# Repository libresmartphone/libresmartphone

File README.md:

Libre Smartphone - Open hardware phone
======================================

This page contains the software used in the open hardware smartphone, related projects files and documentation. Mechanical ([Freecad](http://freecadweb.org/)) and PCB schematic ([Kicad](http://kicad-pcb.org/)) designs will be added here in the future. Visit [libresmartphone.com](http://libresmartphone.com/open-hardware-smartphone/) or our [YouTube channel](https://www.youtube.com/channel/UC1UttFNKDiN2uA525Pe3ijA) for more information.

## Objective

Libresmartphone is a smartphone that can be connected to a bigger screen and used as a desktop computer to edit documents, watch videos, listen to music, edit images, videos and much more.

Our goal is to have a 6" screen, HDMI output, cameras, Bluetooth, WiFi, GPS, 4G or better and GSM. It will also have two or more micro-usb ports that will allow you to connect a printer or other peripherals.

It will be [Open Software](https://en.wikipedia.org/wiki/Open-source_software) and [Open Hardware](https://en.wikipedia.org/wiki/Open-source_hardware), designed with free software (Kicad) to let other users study, change and improve both the software and the hardware.

The design will allow one to add hardware kill switches for the camera, GPS, 4G, GSM.  This offers security & privacy for those who want full control over their devices.

## Roadmap

1. Make a [Raspberry Pi](https://www.raspberrypi.org/) prototype work as desired (Estimated time: 3 months – 1 year)(Estimated cost: <500€):
   * Software to make calls, send/receive SMS (with the [Adafruit 3G Fona](https://www.adafruit.com/product/2696) or similar), import contacts (csv) and take photos in any GNU/linux or BSD OS.
   * GPS navigation with navit.
   * Easy to make case (MDF) / CAD files to 3d print the case.
   * 7" capacitive screen from the Raspberry Pi foundation.
   * Make a manual so every user with a Raspberry Pi can achieve a working prototype easily.

   *The Raspberry Pi prototype will attract a larger user base for the project (currently there are 8 million Raspberry Pi in the market and a lot of their users are DIY enthusiast). Many of them are not willing to pay for an open source smartphone but would love to make calls with the Raspberry Pi, send SMS for their projects, build an simple GPS unit for their car, etc.*

2. Make a prototype with the components more open (Estimated time: 6 months – 4 years)(Estimated cost: 500-40.000€):
   * Use a more open HW board (A64 OLinuXino or similar) instead of the Raspberry Pi.
   * Use a more open HW screen (Manga Screen or similar) or design a 6" capacitive screen if there isn't any open hardware option available at that time (initiate a crowdfunding campaign to let others interested contribute).
   * Use a more open HW modem breakout if there is one available instead of the Adafruit 3G or design a LTE (PLS8-E) or better modem breakout (try to make a crowdfunding campaign to let others interested contribute).

   *The prototype will have replaceable parts if better / smaller alternatives appear in the market.*

   *If no suitable screens or modem breakout are found, a crowdfunding campaign will be made. The reason to make it that way is because there are other people that could want these parts for a different project and help to make it possible faster. Even if there is not enough people willing to support a crowdfunding campaign, the current people interested in making libresmartphone are able to pay Elias Bakken, Nikolaus Schaller or others to make them.*

*When the prototype has the size and requirements desired, libresmartphone development will start part 3.*

3. Libresmartphone final design (Estimated time: <2 years)(Estimated cost: 50.000-200.000€).
   * Design a pcb that has the CPU, GPU, RAM, modem, WiFi, etc in the same board taking in consideration all the designs used in part 2 of the development.
   * Design a case to fit all the components inside that is easy to 3D print. If there are enough people interested an injection case could be made.

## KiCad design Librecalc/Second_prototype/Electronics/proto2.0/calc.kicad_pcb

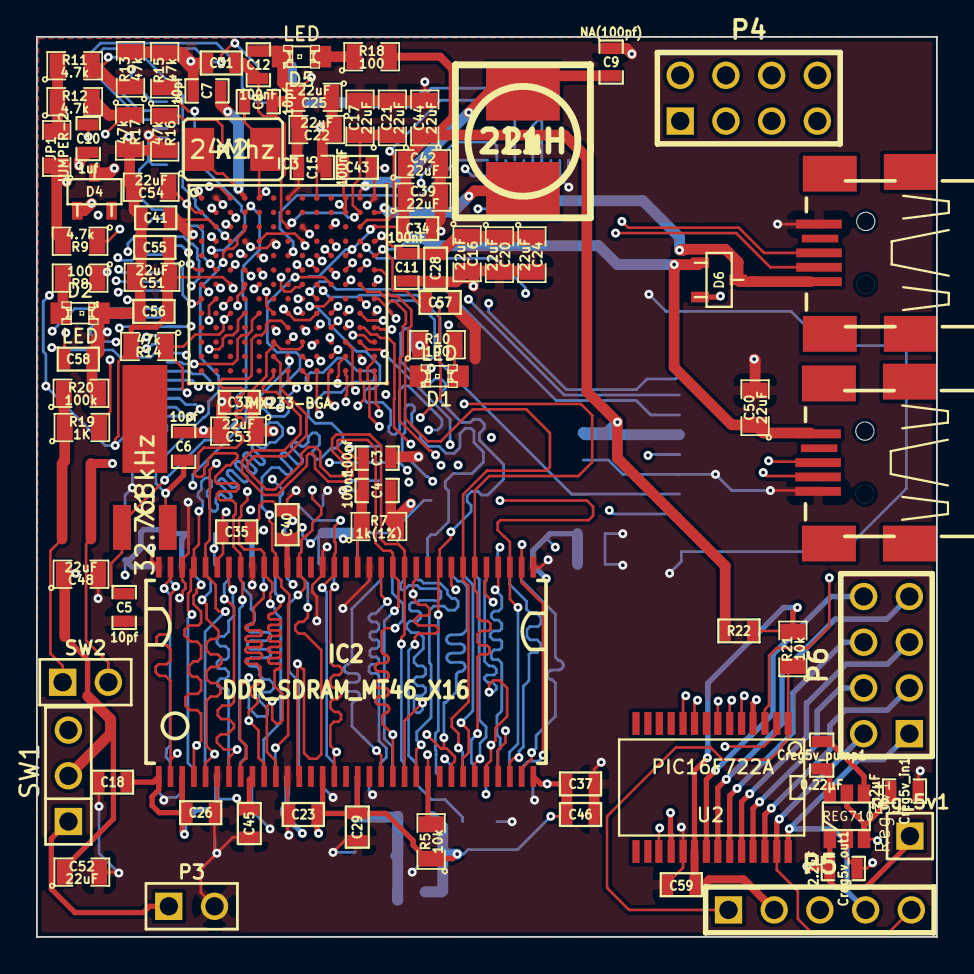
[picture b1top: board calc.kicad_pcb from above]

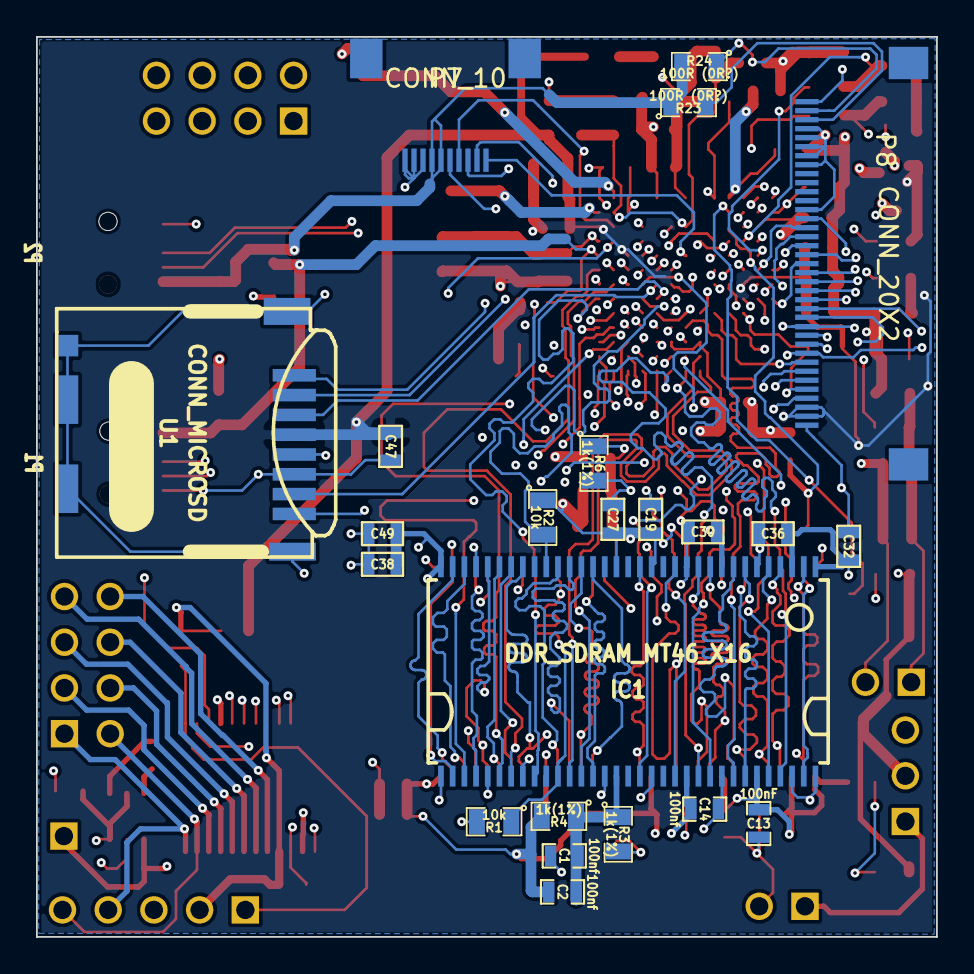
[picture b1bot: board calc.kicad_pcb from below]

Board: 6 copper layers, 50.0 x 50.0 mm, 112 parts (23 on the bottom side), 129 nets.

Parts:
C1, C2, C3, C4, C14: 100nf; SM0603_Capa
C5, C6, C7, C8: 10pf; SM0603_Capa
C9: NA(100pf); SM0603_Capa
C10: 1uf; SM0603_Capa
C11, C12, C13, C15: 100nF; SM0603_Capa
C16, C17, C20, C21, C22, C24, C25, C39, C42, C44, C48, C50, C51, C52, C53, C54: 22uF; SM0805
C18, C23, C27, C30, C32, C36, C38, C41, C59: 100nf; SM0603
C19, C26, C28, C29, C31, C34, C37, C40, C43, C45, C46, C49, C55, C58: 100nF; SM0603
C33, C35, C47, C56, C57: 1uF; SM0603
Creg5v_in1, Creg5v_out1: 2.2µF; SM0603_Capa
Creg5v_pump1: 0.22µF; SM0603_Capa
D1, D2, D5: LED; LED-0805
D4: DIODE; sot23
D6: DOUBLE_SCH_KCOM; sot23
IC1, IC2: DDR_SDRAM_MT46_X16; TSOP66_JEDEC_DDR_SDRAM
IC3: IMX233-BGA; BGA169_0.8mmPitch_11x11mm
JP1: JUMPER-2; SM0805
L1: 22uH; inductor22
P1, P2: CONN_4; CONN_USB_MINI_PIERRE
P3: CONN_2; PIN_ARRAY_2X1
P4, P6: CONN_8; pin_array_4x2
P5: CONN_5; PIN_ARRAY_5x1
P7: CONN_10; FPC10
P8: CONN_20X2; FPC37
R1, R2, R5, R21: 10k; SM0805
R3, R4, R6, R7: 1k(1%); SM0805
R8, R10, R18: 100; SM0805
R9, R11, R12: 4.7k; SM0805
R13, R14, R15, R16, R17: 47k; SM0805
R19: 1K; SM0805
R20: 100k; SM0805
R22: 0R; SM0603
R23, R24: 100R (0R?); SM0805
Reg5v1: REG710; SOT23_6
SW1: SWITCH_INV; PIN_ARRAY_3X1
SW2: SWITCH_PUSHBUTTON; PIN_ARRAY_2X1
U1: CONN_MICROSD; Memory_Card_microSD_DM3CS-SF
U2: PIC16F722A; SSOP28
X1: 32.768kHz; xtal32.768
X2: 24Mhz; SMDXTAL24mhz
reg_5v1: CONN_1; PIN_ARRAY_1

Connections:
3V3PIC: C59.2, P5.2, R21.2, R22.2, U2.20
5VOUT: D6.2, P2.1, P7.6, P7.7, R23.1, R24.2
5VREG: Creg5v_out1.1, D6.3, Reg5v1.1, reg_5v1.1
+2.5V: C2.2, C4.2, C13.1, C14.1, C18.1, C19.1, C23.1, C26.1, C27.1, C29.1, C30.1, C32.1, C33.1, C35.1, C36.1, C37.1, C38.1, C40.1, C45.1, C46.1, C49.1, C53.1, IC1.1, IC1.3, IC1.9, IC1.15, IC1.18, IC1.33, IC1.55, IC1.61, IC2.1, IC2.3, IC2.9, IC2.15, IC2.18, IC2.33, IC2.55, IC2.61, IC3.C10, IC3.L6, IC3.L8, IC3.L10, R2.1, R4.2, R5.1, R7.2
+3.3V: C34.1, C39.1, C42.1, C44.1, C47.1, C51.1, C55.1, C56.1, IC3.C13, IC3.E11, IC3.G3, JP1.1, P8.2, P8.3, R9.2, R14.2, R18.2, R22.1, U1.4
/Processor/SD_CLOCK: IC3.D12, U1.5
/Processor/U_RX: IC3.C3, P1.3, R9.1
/Processor/U_TX: IC3.D2, P1.2, R8.1
DDRA0: IC1.29, IC2.29, IC3.K13
DDRA1: IC1.30, IC2.30, IC3.K12
DDRA2: IC1.31, IC2.31, IC3.J13
DDRA3: IC1.32, IC2.32, IC3.K11
DDRA4: IC1.35, IC2.35, IC3.G10
DDRA5: IC1.36, IC2.36, IC3.G12
DDRA6: IC1.37, IC2.37, IC3.F12
DDRA7: IC1.38, IC2.38, IC3.G11
DDRA8: IC1.39, IC2.39, IC3.G13
DDRA9: IC1.40, IC2.40, IC3.F13
DDRA10: IC1.28, IC2.28, IC3.J12
DDRA11: IC1.41, IC2.41, IC3.H10
DDRA12: IC1.42, IC2.42, IC3.H13
DDR_BA0: IC1.26, IC2.26, IC3.L13
DDR_BA1: IC1.27, IC2.27, IC3.L12
DDR_CAS: IC1.22, IC2.22, IC3.M13
DDR_CE0n: IC2.24, IC3.J10, R5.2
DDR_CE1n: IC1.24, IC3.H12, R2.2
DDR_CKE: IC1.44, IC2.44, IC3.F11, R1.1
DDR_CLK: IC1.45, IC2.45, IC3.M6
DDR_CLKn: IC1.46, IC2.46, IC3.N6
DDR_DO0: IC1.2, IC2.2, IC3.K10
DDR_DO1: IC1.4, IC2.4, IC3.M10
DDR_DO2: IC1.5, IC2.5, IC3.N11
DDR_DO3: IC1.7, IC2.7, IC3.N10
DDR_DO4: IC1.8, IC2.8, IC3.M11
DDR_DO5: IC1.10, IC2.10, IC3.K9
DDR_DO6: IC1.11, IC2.11, IC3.L11
DDR_DO7: IC1.13, IC2.13, IC3.L9
DDR_DO8: IC1.54, IC2.54, IC3.N9
DDR_DO9: IC1.56, IC2.56, IC3.N8
DDR_DO10: IC1.57, IC2.57, IC3.M8
DDR_DO11: IC1.59, IC2.59, IC3.K7
DDR_DO12: IC1.60, IC2.60, IC3.L7
DDR_DO13: IC1.62, IC2.62, IC3.K6
DDR_DO14: IC1.63, IC2.63, IC3.N7
DDR_DO15: IC1.65, IC2.65, IC3.M7
DDR_DQM0: IC1.20, IC2.20, IC3.M12
DDR_DQM1: IC1.47, IC2.47, IC3.M9
DDR_DQS0: IC1.16, IC2.16, IC3.N12
DDR_DQS1: IC1.51, IC2.51, IC3.K8
DDR_RAS: IC1.23, IC2.23, IC3.N13
DDR_WEn: IC1.21, IC2.21, IC3.J11
GND: C1.2, C3.2, C5.1, C6.1, C7.1, C8.1, C9.1, C10.2, C11.2, C12.2, C13.2, C14.2, C15.2, C16.2, C17.2, C18.2, C19.2, C20.2, C21.2, C22.2, C23.2, C24.2, C25.2, C26.2, C27.2, C28.2, C29.2, C30.2, C31.2, C32.2, C33.2, C34.2, C35.2, C36.2, C37.2, C38.2, C39.2, C40.2, C41.2, C42.2, C43.2, C44.2, C45.2, C46.2, C47.2, C48.2, C49.2, C50.2, C51.2, C52.2, C53.2, C54.2, C55.2, C56.2, C57.2, C58.2, C59.1, Creg5v_in1.2, Creg5v_out1.2, D1.2, D2.2, D5.2, IC1.6, IC1.12, IC1.34, IC1.48, IC1.52, IC1.58, IC1.64, IC1.66, IC2.6, IC2.12, IC2.34, IC2.48, IC2.52, IC2.58, IC2.64, IC2.66, IC3.A2, IC3.A7, IC3.A13, IC3.C8, IC3.D4, IC3.D6, IC3.E9, IC3.J7, IC3.J9, P1.1, P2.4, P3.2, P5.3, P7.8, P7.9, P7.10, P8.1, P8.25, P8.30, P8.31, P8.32, P8.33, P8.34, P8.37, R1.2, R3.2, R6.2, R13.2, R15.2, R16.2, R17.2, R20.2, Reg5v1.2, U1.6, U1.9, U2.19
KEYBOARD_UART_RX: IC3.J8, U2.18
KEYBOARD_UART_TX: IC3.H8, U2.17
LCD_CS: IC3.F8, P8.4
LCD_D0: IC3.D3, P8.9, R11.2, R13.1
LCD_D1: IC3.E2, P8.10, R15.1
LCD_D2: IC3.E4, P8.11, R16.1
LCD_D3: IC3.F1, P8.12, R12.2, R17.1
LCD_D4: IC3.F3, P8.13
LCD_D5: IC3.F5, P8.14
LCD_D6: IC3.G2, P8.15
LCD_D7: IC3.G5, P8.16
LCD_D8: IC3.H2, P8.17
LCD_D9: IC3.H3, P8.18
LCD_D10: IC3.H1, P8.19
LCD_D11: IC3.G4, P8.20
LCD_D12: IC3.G1, P8.21
LCD_D13: IC3.F4, P8.22
LCD_D14: IC3.F2, P7.5, P8.23
LCD_D15: IC3.E5, P7.3, P8.24
LCD_RD: IC3.G8, P8.7
LCD_RS: IC3.J3, P8.5, R14.1
LCD_RST: IC3.J5, P8.8
LCD_WR: IC3.J4, P8.6
unnamed: C3.1, C4.1, IC2.49, R6.1, R7.1
unnamed: C1.1, C2.1, IC1.49, R3.1, R4.1
unnamed: D2.1, R8.2
unnamed: C10.1, IC3.A3
unnamed: JP1.2, R11.1, R12.1
unnamed: IC3.F10, U1.1
unnamed: IC3.D10, R10.1
unnamed: IC3.E10, U1.2
unnamed: C9.2, IC3.A12, L1.2
unnamed: IC3.H9, U1.3
unnamed: D1.1, R10.2
unnamed: C6.2, IC3.C4, X1.1
unnamed: C5.2, IC3.B4, X1.2
unnamed: IC3.B13, L1.1
unnamed: C8.2, IC3.A5, X2.2
unnamed: IC3.G9, U1.7
unnamed: IC3.F9, U1.8
unnamed: C7.2, IC3.A4, X2.1
unnamed: IC3.B2, P2.2
unnamed: IC3.A1, P2.3
unnamed: Creg5v_pump1.1, Reg5v1.6
unnamed: Creg5v_pump1.2, Reg5v1.4
unnamed: D5.1, R18.1
unnamed: R19.1, R20.1, SW2.1
unnamed: P3.1, SW1.1
unnamed: P5.5, P6.2, U2.27
unnamed: P6.8, U2.21
unnamed: P6.6, U2.23
unnamed: P6.4, U2.25
unnamed: P4.5, U2.5
unnamed: P6.7, U2.22
unnamed: P6.3, U2.26
unnamed: P6.5, U2.24
unnamed: P4.6, U2.4
unnamed: P4.1, U2.9
unnamed: P4.2, U2.10
unnamed: P4.3, U2.7
unnamed: P4.4, U2.6
unnamed: P4.7, U2.3
unnamed: P4.8, U2.2
unnamed: P5.4, P6.1, U2.28
unnamed: P5.1, R21.1, U2.1
unnamed: P8.36, R24.1
unnamed: P8.35, R23.2
POWER_5V_IN: C50.1, C57.1, D6.1, IC3.E13, P1.4
PSWITCH: C58.1, IC3.B3, R19.2
SHARP_PWM: IC3.C12, P7.4
SPI_CLK: IC3.E7, P7.1
SPI_CMD: IC3.J6, P7.2
VDD4P2: C15.1, C22.1, C25.1, D4.2, IC3.A9
VDDA: C12.1, C17.1, C21.1, C31.1, IC3.B12, IC3.C7
VDDD: C11.1, C16.1, C20.1, C24.1, C28.1, IC3.D5, IC3.D8, IC3.D13
VDD_BATT: C43.1, C48.1, C52.1, C54.1, Creg5v_in1.1, D4.1, IC3.A11, IC3.B1, IC3.B11, Reg5v1.3, Reg5v1.5, SW1.2
VDD_XTAL: C41.1, IC3.C2, SW2.2

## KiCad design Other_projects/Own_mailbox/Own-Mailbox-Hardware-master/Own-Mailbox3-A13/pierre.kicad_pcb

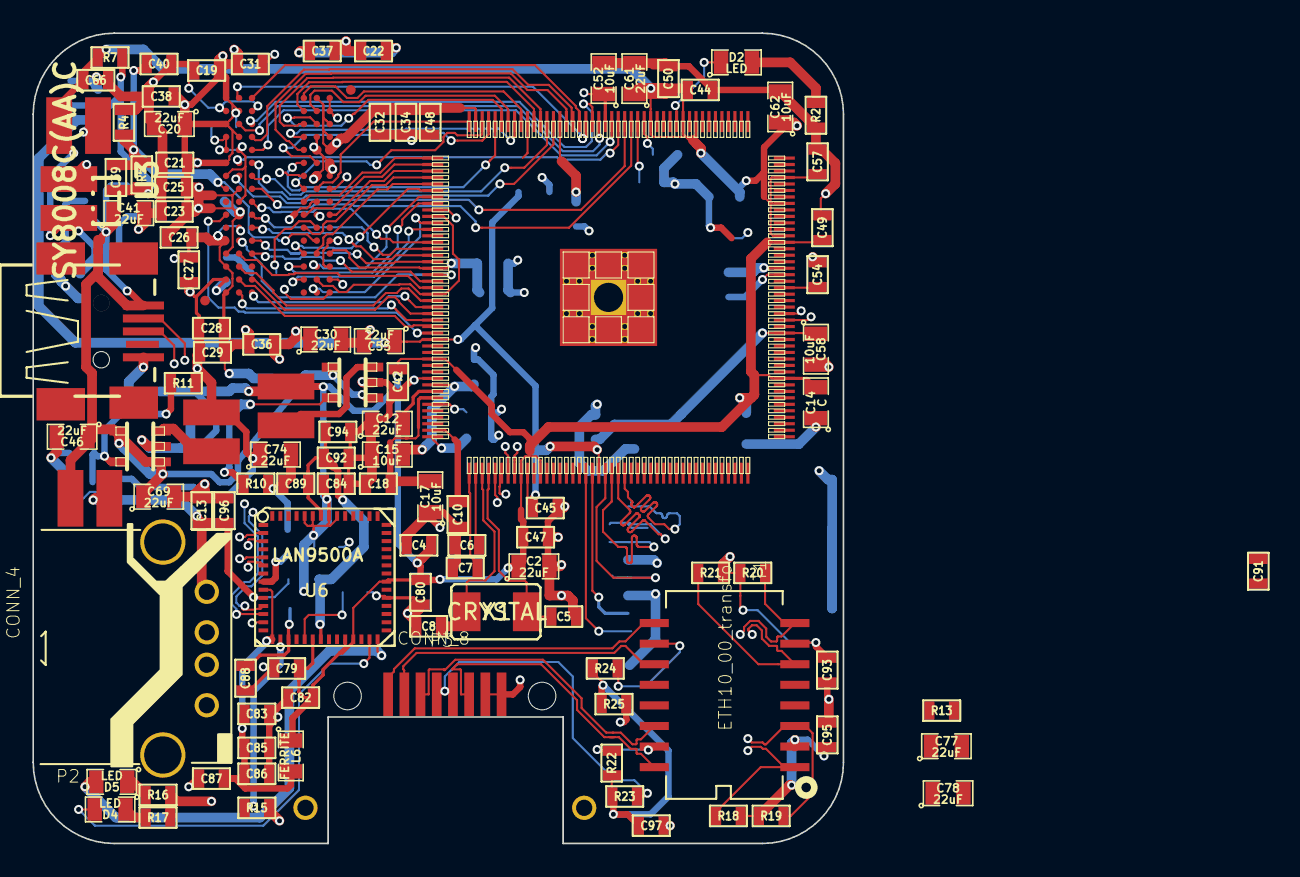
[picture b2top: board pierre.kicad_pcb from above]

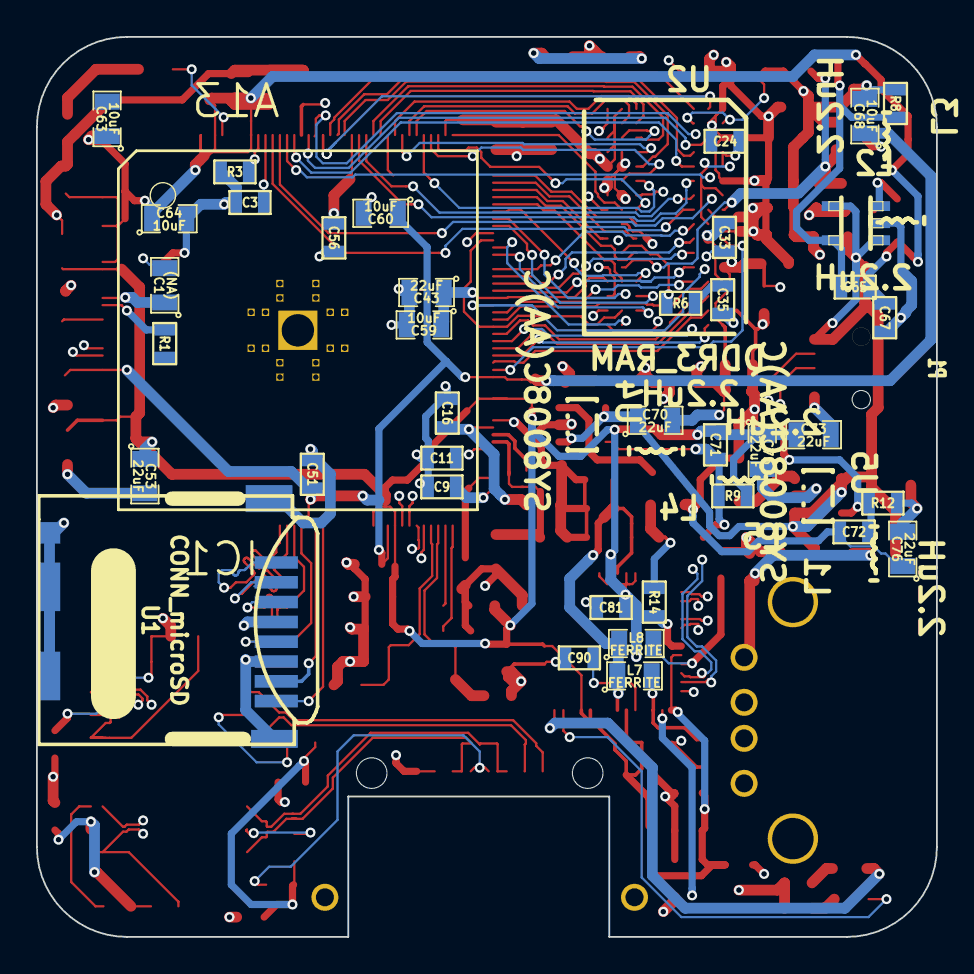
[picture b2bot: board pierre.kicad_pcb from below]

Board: 4 copper layers, 50.0 x 50.0 mm, 145 parts (38 on the bottom side), 114 nets.

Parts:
C1: (NA); SM0805
C2, C12, C20, C30, C41, C43, C46, C53, C55, C61, C69, C70, C73, C74, C75, C76, C77, C78: 22uF; SM0805
C3, C4, C13, C16, C18, C19, C21, C22, C23, C24, C25, C26, C27, C28, C29, C31, C32, C33, C34, C35, C36, C37, C38, C39, C40, C42, C44, C45, C47, C48, C49, C50, C51, C54, C56, C57, C79, C80, C81, C82, C83, C84, C85, C86, C87, C88, C92, C93, C94, C95, C96: 100nF; SM0603
C5, C8, C90, C91: 10pF; SM0603
C6, C7, C9, C10: 1nF; SM0603
C11, C89, C97: 1uF; SM0603
C14: C; SM0805
C15, C17, C52, C58, C59, C60, C62, C63, C64, C68: 10uF; SM0805
C65, C71, C72: 22pF; SM0603
C66, C67: 22uF; SM0603
D2, D4, D5: LED; SM0805
IC1: A13; TQFP176
L1, L2, L3, L4, L5: 2.2uH; CD32
L6, L7, L8: FERRITE; SM0805
P1: CONN_4; CONN_USB_MINI_PIERRE
P2: CONN_4; USB-A_TH
P3: CONN_8; RJ45_LP_RA_SMT
R1: 47k; SM0603
R2: 500R; SM0603
R3: 240R; SM0603
R4, R5: 1k(1%); SM0603
R6: 240R(1%); SM0603
R7: 2k(1%); SM0603
R8: 1.5k(1%); SM0603
R9: 100k(1%); SM0603
R10: 22k(1%); SM0603
R11: 4.99k(1%); SM0603
R12: 3.3k(1%); SM0603
R13: 2.2k; SM0603
R14, R15: R; SM0603
R16, R17: 100R; SM0603
R18, R19, R20, R21: 50R; SM0603
R22, R23, R24, R25: 75R; SM0603
T1: ETH10_00_transfo; H1601CG
U1: CONN_microSD; Memory_Card_microSD_DM3CS-SF
U2: DDR3_RAM; FBGA96
U3, U4, U5: SY8008C(AA)C; SOT23-5
U6: LAN9500A; QFN48
X1: CRYSTAL; SMDXTAL24mhz

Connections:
1V5: C19.1, C20.1, C21.1, C22.1, C23.1, C24.1, C25.1, C26.1, C27.1, C28.1, C29.1, C30.1, C31.1, C32.1, C33.1, C34.1, C35.1, C36.1, C37.1, C38.1, C39.1, C43.1, C48.1, C52.1, C56.1, C59.1, C72.1, C74.1, C76.1, IC1.23, IC1.30, IC1.43, IC1.53, IC1.62, L5.2, R5.1, R11.1, U2.A1, U2.A8, U2.B2, U2.C1, U2.C9, U2.D2, U2.D9, U2.E9, U2.F1, U2.G7, U2.H2, U2.H9, U2.K2, U2.K8, U2.N1, U2.N9, U2.R1, U2.R9
3VA: C12.2, C77.1, C78.1, IC1.81, R13.1
+5V: C41.1, C46.1, C69.1, C70.1, L1.2, P1.1, U3.1, U3.4, U4.1, U4.4, U5.1, U5.4
/Erhernet/RX+: P3.7, T1.11
/Erhernet/RX-: P3.8, T1.9
/Erhernet/TX+: P3.3, T1.16
/Erhernet/TX-: P3.6, T1.14
DDR3_A00: IC1.64, U2.N3
DDR3_A01: IC1.52, U2.P7
DDR3_A03: IC1.65, U2.N2
DDR3_A04: IC1.51, U2.P8
DDR3_A05: IC1.67, U2.P2
DDR3_A06: IC1.54, IC1.66, U2.R8
DDR3_A07: IC1.71, U2.R2
DDR3_A08: IC1.55, U2.T8
DDR3_A09: IC1.69, U2.R3
DDR3_A10: IC1.48, U2.L7
DDR3_A11: IC1.56, U2.R7
DDR3_A12: IC1.50, U2.N7
DDR3_A13: IC1.68, U2.T3
DDR3_BA0: IC1.63, U2.M2
DDR3_BA1: IC1.49, U2.N8
DDR3_BA2: IC1.61, U2.M3
DDR3_CAS: IC1.59, U2.K3
DDR3_CK: IC1.45, U2.J7
DDR3_CKE: IC1.47, U2.K9
DDR3_CK_N: IC1.46, U2.K7
DDR3_D00: IC1.22, U2.E3
DDR3_D01: IC1.40, U2.F7
DDR3_D02: IC1.21, U2.F2
DDR3_D03: IC1.41, U2.F8
DDR3_D04: IC1.19, U2.H3
DDR3_D05: IC1.44, U2.H8
DDR3_D06: IC1.20, U2.G2
DDR3_D07: IC1.42, U2.H7
DDR3_D08: IC1.37, U2.D7
DDR3_D09: IC1.25, U2.C3
DDR3_D10: IC1.39, U2.C8
DDR3_D11: IC1.24, U2.C2
DDR3_D12: IC1.36, U2.A7
DDR3_D13: IC1.26, U2.A2
DDR3_D14: IC1.38, U2.B8
DDR3_D15: IC1.27, U2.A3
DDR3_DM0: IC1.29, U2.E7
DDR3_DM1: IC1.28, U2.D3
DDR3_DQS0: IC1.31, U2.F3
DDR3_DQS0_N: IC1.32, U2.G3
DDR3_DQS1: IC1.33, U2.C7
DDR3_DQS1_N: IC1.34, U2.B7
DDR3_ODT: IC1.72, U2.K1
DDR3_RAS: IC1.58, U2.J3
DDR3_RST: IC1.70, U2.T2
DDR3_WE: IC1.60, U2.L3
GND: C1.2, C2.2, C3.2, C4.1, C5.1, C6.1, C7.1, C8.1, C9.1, C10.1, C11.1, C12.1, C13.2, C14.1, C15.1, C16.1, C17.1, C18.1, C19.2, C20.2, C21.2, C22.2, C23.2, C24.2, C25.2, C26.2, C27.2, C28.2, C29.2, C30.2, C31.2, C32.2, C33.2, C34.2, C35.2, C36.2, C37.2, C38.2, C40.2, C41.2, C42.2, C43.2, C44.2, C45.2, C46.2, C47.2, C48.2, C49.2, C50.2, C51.2, C52.2, C53.2, C54.2, C55.2, C56.2, C57.2, C58.2, C59.2, C60.2, C61.2, C62.2, C63.2, C64.2, C66.2, C67.2, C68.2, C69.2, C70.2, C73.2, C74.2, C75.2, C76.2, C77.2, C78.2, C79.2, C80.2, C81.2, C82.2, C83.2, C84.2, C85.2, C86.2, C87.2, C88.2, C89.2, C90.1, C91.1, C92.2, C93.1, C94.2, C95.2, C96.2, C97.1, IC1.79, P1.4, P2.4, R2.2, R3.2, R4.2, R6.2, R8.2, R10.2, R12.2, R13.2, R14.1, R15.1, U1.6, U1.9, U2.A9, U2.B1, U2.B3, U2.B9, U2.D1, U2.D8, U2.E1, U2.E2, U2.E8, U2.F9, U2.G1, U2.G8, U2.G9, U2.J2, U2.J8, U2.L2, U2.M1, U2.M9, U2.P1, U2.P9, U2.T1, U2.T9, U3.2, U4.2, U5.2, U6.13, U6.33
LED1: D4.2, U6.27
LED2: D5.2, U6.28
unnamed: C1.1, IC1.159
unnamed: C3.1, IC1.18
unnamed: C6.2, IC1.90
unnamed: C7.2, IC1.89
unnamed: C9.2, IC1.88
unnamed: C10.2, IC1.87
unnamed: C11.2, IC1.83
unnamed: C13.1, L1.1, P2.1
unnamed: C15.2, C16.2, IC1.80
unnamed: C17.2, C18.2, IC1.82
unnamed: C39.2, C40.1, R4.1, R5.2, U2.H1, U2.M8
unnamed: C65.2, R7.2, R8.1, U3.5
unnamed: C71.2, R9.2, R10.1, U4.5
unnamed: C72.2, R11.2, R12.1, U5.5
unnamed: C90.2, U6.19
unnamed: C91.2, U6.18
unnamed: C97.2, R22.1, R23.1, R24.1, R25.1
unnamed: D2.1, IC1.12
unnamed: D2.2, R2.1
unnamed: D4.1, R17.1
unnamed: D5.1, R16.1
unnamed: IC1.17, R3.1
unnamed: IC1.158, R1.2
unnamed: L2.1, U3.3
unnamed: L4.1, U4.3
unnamed: L5.1, U5.3
unnamed: P3.1, P3.2, R25.2
unnamed: P3.4, P3.5, R23.2
unnamed: R6.1, U2.L8
unnamed: R14.2, U6.8
unnamed: R15.2, U6.16
unnamed: R22.2, T1.15
unnamed: R24.2, T1.10
RPX_N: R20.1, T1.8, U6.5
RPX_P: R21.1, T1.6, U6.6
SDC0_CLK: IC1.110, U1.5
SDC0_CMD: IC1.111, U1.3
SDC0_D0: IC1.108, U1.7
SDC0_D1: IC1.107, U1.8
SDC0_D2: IC1.113, U1.1
SDC0_D3: IC1.112, U1.2
TPX_N: R19.2, T1.3, U6.2
TPX_P: R18.2, T1.1, U6.3
UART1_RX: IC1.151, P1.3
UART1_TX: IC1.152, P1.2
USB_ETH_N: IC1.93, U6.11
USB_ETH_P: IC1.94, U6.12
USB_HOST_N: IC1.95, P2.2
USB_HOST_P: IC1.96, P2.3
VCC: C2.1, C4.2, C14.2, C42.1, C47.1, C49.1, C53.1, C71.1, C73.1, C75.1, C79.1, C80.1, C81.1, C82.1, C84.1, C93.2, C95.1, IC1.76, IC1.97, IC1.100, IC1.142, IC1.163, L4.2, L6.1, R9.1, R16.2, R17.2, R18.1, R19.1, R20.2, R21.2, T1.2, T1.7, U1.4, U6.20, U6.24, U6.25, U6.35, U6.48, U6.49, U6.51, U6.52
VDD33A: C83.1, C85.1, C86.1, C87.1, L6.2, U6.4, U6.7, U6.9, U6.15
VDDBUSPLL: C88.1, L7.2, U6.17
VDDCORE: C89.1, C92.1, C94.1, L7.1, L8.1, U6.21, U6.50
VDDPLL: C96.1, L8.2, U6.10
VDD_CPU: C44.1, C50.1, C54.1, C57.1, C61.1, C62.1, C63.1, C64.1, C65.1, C66.1, C67.1, IC1.9, IC1.11, IC1.16, IC1.156, IC1.164, IC1.169, IC1.173, L2.2, L3.1, R7.1
VDD_INT: C45.1, C51.1, C55.1, C58.1, C60.1, C68.1, IC1.35, IC1.73, IC1.98, IC1.109, IC1.149, L3.2
X1_N: C5.2, IC1.92, X1.1
X1_P: C8.2, IC1.91, X1.2

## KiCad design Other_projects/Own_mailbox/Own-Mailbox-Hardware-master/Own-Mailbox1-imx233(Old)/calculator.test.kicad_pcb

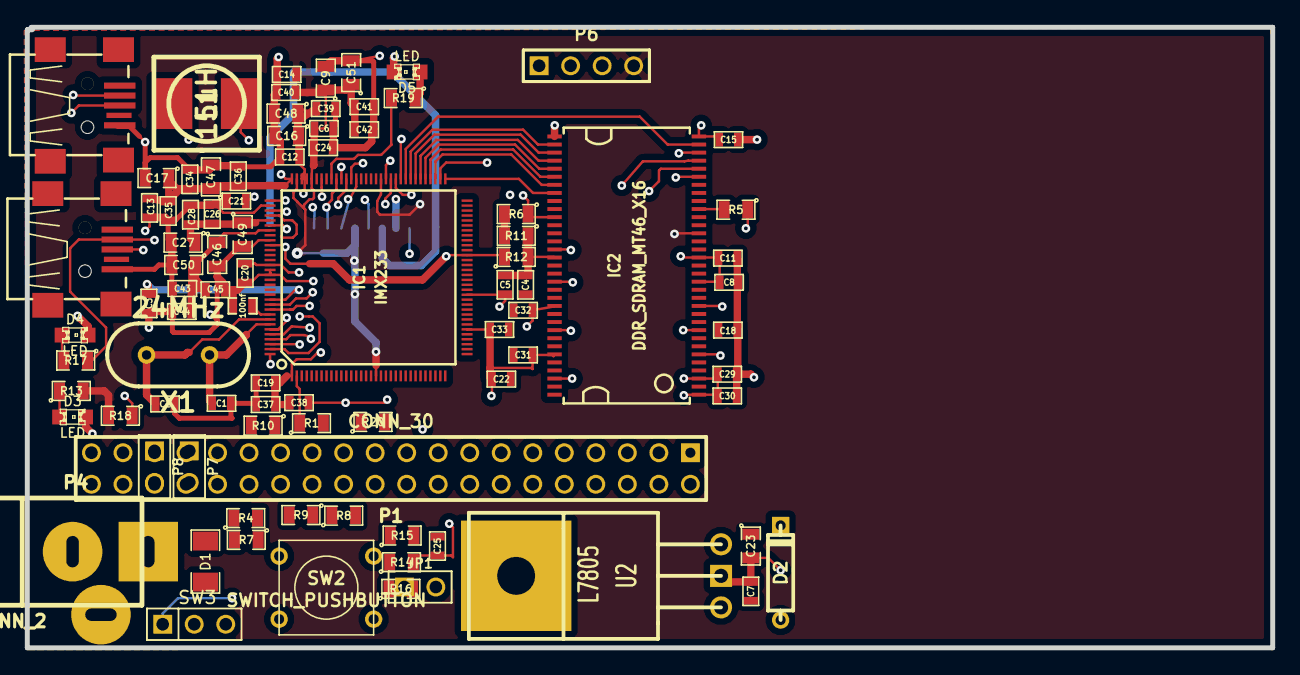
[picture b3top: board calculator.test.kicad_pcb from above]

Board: 4 copper layers, 100.4 x 50.0 mm, 90 parts (1 on the bottom side), 108 nets.

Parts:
C1, C2: 10pf; SM0603_Capa
C3, C7: 1uf; SM0603
C4, C5: 100nf; SM0603_Capa
C6, C8, C11, C12, C13, C15, C18, C25, C26, C37, C38, C40, C41, C44: 100nF; SM0603_Capa
C9, C16, C17, C23, C27, C46, C47, C48, C49, C50, C51: 22uF; SM0805
C10: 100nf; SM0603_Opendous
C14, C19, C20: 0.01uF; SM0603_Capa
C21: 1uF; SM0603_Capa
C22, C24, C28, C35, C36, C39, C42, C45: 1uF; SM0603
C29, C30, C31, C32, C33, C34: 100nF; SM0603
C43: 10nF; SM0603
D1: ZENER; SM1206
D2: D_SCHOTTKY; D3
D3, D4, D5: LED; LED-0805
IC1: IMX233; LQFP128_14x14mm_0.4mmPitch_iMX233
IC2: DDR_SDRAM_MT46_X16; TSOP66_JEDEC_DDR_SDRAM
JP1: Jumper-2; PIN_ARRAY_2X1
L1: 15uH; inductor22
P1: CONN_30; PIN_ARRAY_20X2
P3, P5: CONN_4; CONN_USB2_MiniB_SMT
P4: CONN_2; JACK_ALIM
P6: CONN_4; PIN_ARRAY_4x1
P7, P8: CONN_2; PIN_ARRAY_2X1
R1, R4, R8, R9, R18: 4.7k; SM0805
R5, R6, R16: 10k; SM0805
R7, R10, R20: 47k; SM0805
R11, R12: 1k(1%); SM0805
R13, R17, R19: 100; SM0805
R14: 1K; SM0805
R15: 100k; SM0805
SW2: SWITCH_PUSHBUTTON; SW_PUSH_SMALL
SW3: SWITCH_INV; PIN_ARRAY_3X1
U1: CONN_MICROSD; Memory_Card_microSD_DM3CS-SF
U2: L7805; LM78XX
X1: 24MHz; HC-49V

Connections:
+2.5V: C5.1, C8.1, C11.1, C15.1, C18.1, C22.1, C29.1, C30.1, C31.1, C32.1, C33.1, IC1.38, IC1.45, IC1.53, IC1.106, IC2.1, IC2.3, IC2.9, IC2.15, IC2.18, IC2.33, IC2.55, IC2.61, R5.1, R12.1
+3.3V: C6.1, C9.1, C14.1, C24.1, C40.1, C41.1, C42.1, C51.1, IC1.18, IC1.92, IC1.95, JP1.1, P6.4, R13.2, R16.2, R18.2, R20.2, U1.4
+5V: C21.1, D1.2, IC1.102, P1.30, SW3.1
/LCD_D0: IC1.2, P1.28, R1.1, R7.1
/LCD_D1: IC1.3, P1.27, R8.1
/LCD_D2: IC1.4, P1.26, R9.1
/LCD_D3: IC1.5, P1.25, R4.1, R10.1
/LCD_RS: IC1.14, P1.16, R20.1
/SD_CLOCK: IC1.90, U1.5
/SD_CMD: IC1.83, U1.3
/U_RX: IC1.125, P3.3, R18.1
/U_TX: IC1.126, P3.2, R17.1
DDRA0: IC1.76, IC2.29
DDRA1: IC1.75, IC2.30
DDRA2: IC1.74, IC2.31
DDRA3: IC1.73, IC2.32
DDRA4: IC1.72, IC2.35
DDRA5: IC1.71, IC2.36
DDRA6: IC1.70, IC2.37
DDRA7: IC1.69, IC2.38
DDRA8: IC1.68, IC2.39
DDRA9: IC1.67, IC2.40
DDRA10: IC1.66, IC2.28
DDRA11: IC1.65, IC2.41
DDRA12: IC1.64, IC2.42
DDR_BA0: IC1.79, IC2.26
DDR_BA1: IC1.80, IC2.27
DDR_CAS: IC1.61, IC2.22
DDR_CE0n: IC1.63, IC2.24, R5.2
DDR_CKE: IC1.78, IC2.44, R6.1
DDR_CLK: IC1.36, IC2.45
DDR_CLKn: IC1.37, IC2.46
DDR_DO0: IC1.41, IC2.2
DDR_DO1: IC1.43, IC2.4
DDR_DO2: IC1.42, IC2.5
DDR_DO3: IC1.44, IC2.7
DDR_DO4: IC1.47, IC2.8
DDR_DO5: IC1.48, IC2.10
DDR_DO6: IC1.49, IC2.11
DDR_DO7: IC1.50, IC2.13
DDR_DO8: IC1.51, IC2.54
DDR_DO9: IC1.52, IC2.56
DDR_DO10: IC1.54, IC2.57
DDR_DO11: IC1.55, IC2.59
DDR_DO12: IC1.57, IC2.60
DDR_DO13: IC1.58, IC2.62
DDR_DO14: IC1.60, IC2.63
DDR_DO15: IC1.59, IC2.65
DDR_DQM0: IC1.46, IC2.20
DDR_DQM1: IC1.56, IC2.47
DDR_DQS0: IC1.39, IC2.16
DDR_DQS1: IC1.40, IC2.51
DDR_RAS: IC1.62, IC2.23
DDR_WEn: IC1.77, IC2.21
GND: C1.1, C2.1, C3.2, C4.2, C6.2, C7.2, C8.2, C9.2, C10.2, C11.2, C12.2, C13.2, C14.2, C15.2, C16.2, C17.2, C18.2, C19.2, C20.2, C21.2, C22.2, C23.2, C24.2, C25.2, C26.2, C27.2, C28.2, C29.2, C30.2, C31.2, C32.2, C33.2, C34.2, C35.2, C36.2, C37.2, C38.2, C39.2, C40.2, C41.2, C42.2, C43.2, C44.2, C45.2, C46.2, C47.2, C48.2, C49.2, C50.2, C51.2, D1.1, D3.2, D4.2, D5.2, IC1.30, IC1.35, IC1.98, IC1.105, IC1.111, IC1.112, IC1.118, IC2.6, IC2.12, IC2.34, IC2.48, IC2.52, IC2.58, IC2.64, IC2.66, P1.13, P3.4, P4.1, P5.4, P6.1, P8.2, R6.2, R7.2, R8.2, R9.2, R10.2, R11.2, R15.2, U1.6, U1.9, U2.GND
unnamed: IC1.25, P1.7
unnamed: IC1.28, P1.1
unnamed: IC1.26, P1.3
unnamed: IC1.23, P1.9
unnamed: IC1.19, P1.11
unnamed: IC1.87, U1.2
unnamed: IC1.85, U1.8
unnamed: IC1.15, P1.18
unnamed: IC1.17, P1.20
unnamed: IC1.8, P1.22
unnamed: IC1.6, P1.24
unnamed: IC1.13, P1.14
unnamed: IC1.99, L1.2
unnamed: C3.1, IC1.117
unnamed: IC1.97, L1.1
unnamed: IC1.10, P1.29
unnamed: IC1.7, P1.23
unnamed: IC1.9, P1.21
unnamed: IC1.11, P1.19
unnamed: IC1.12, P1.17
unnamed: IC1.16, P1.15
unnamed: IC1.21, P7.2
unnamed: IC1.127, P6.2
unnamed: IC1.88, R19.2
unnamed: D4.1, R17.2
unnamed: IC1.128, P6.3
unnamed: IC1.123, P5.2
unnamed: IC1.124, P5.3
unnamed: JP1.2, R1.2, R4.2
unnamed: IC1.86, U1.1
unnamed: IC1.84, U1.7
unnamed: IC1.22, P1.10
unnamed: IC1.20, P1.12
unnamed: IC1.24, P1.8
unnamed: IC1.27, P1.6
unnamed: IC1.29, P1.2
unnamed: D5.1, R19.1
unnamed: IC1.33, P7.1
unnamed: C4.1, C5.2, IC2.49, R11.1, R12.2
unnamed: C7.1, D2.1, U2.VI
unnamed: R14.1, R15.1, SW2.1
unnamed: C23.1, SW3.2, U2.VO
unnamed: D3.1, R13.1
unnamed: D2.2, P4.2
unnamed: R16.1, SW2.2
PSWITCH: C25.1, IC1.119, R14.2
VDD4P2: C26.1, C27.1, C28.1, C49.1, IC1.101
VDDA: C13.1, C17.1, C20.1, C34.1, C35.1, C36.1, C47.1, IC1.96, IC1.110
VDDD: C12.1, C16.1, C19.1, C37.1, C38.1, C39.1, C48.1, IC1.1, IC1.93, IC1.94
VDD_BATT: C43.1, C44.1, C45.1, C46.1, C50.1, IC1.100, IC1.103, P8.1
VDD_XTAL: C10.1, IC1.120
XTALI: C1.2, IC1.122, X1.1
XTALO: C2.2, IC1.121, X1.2

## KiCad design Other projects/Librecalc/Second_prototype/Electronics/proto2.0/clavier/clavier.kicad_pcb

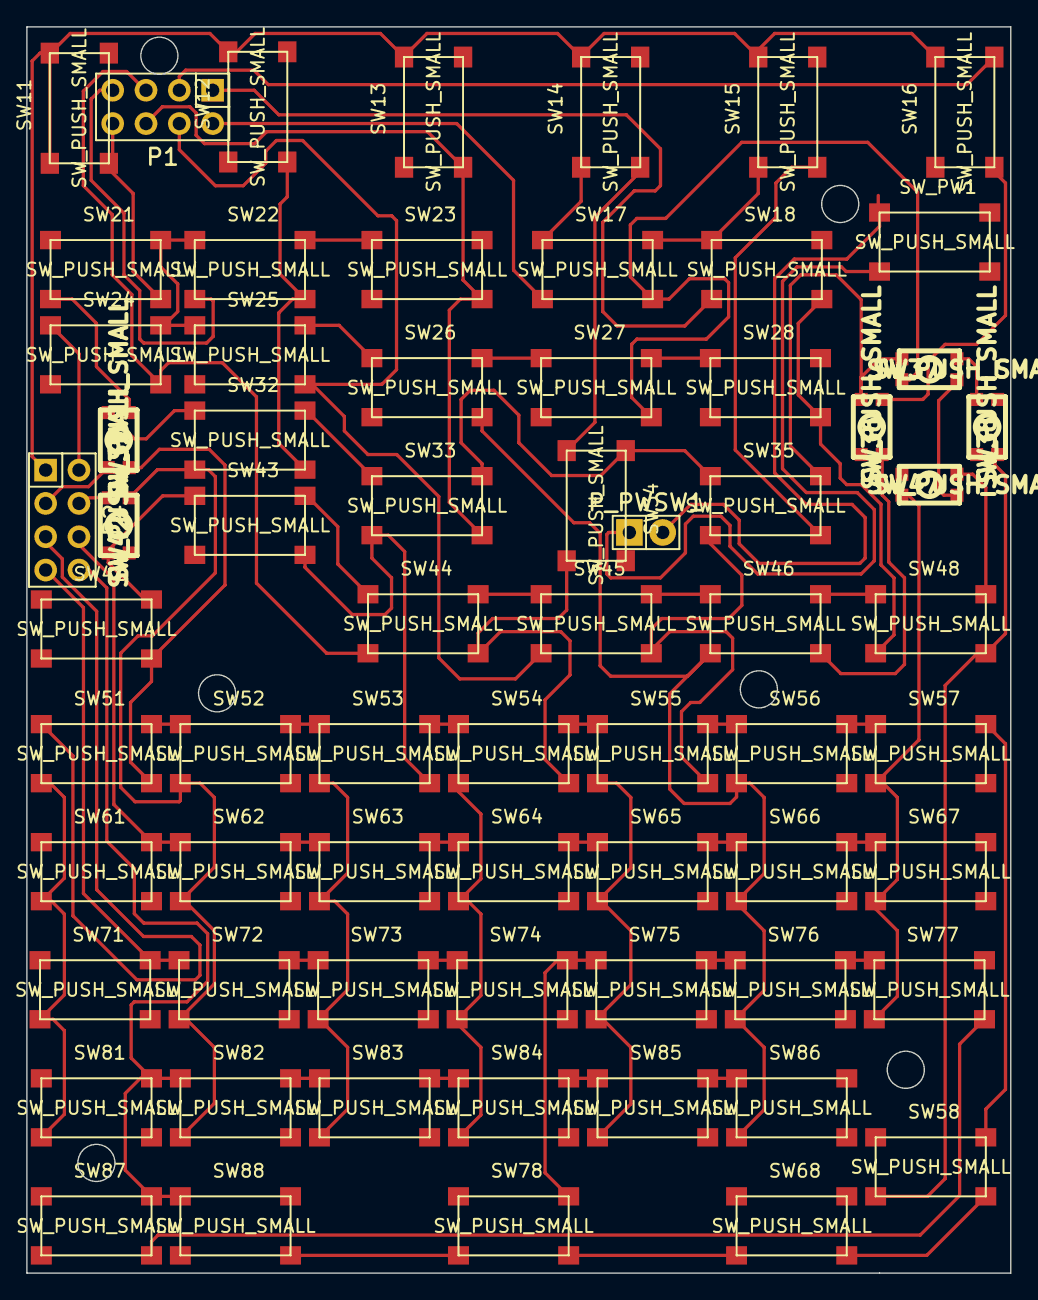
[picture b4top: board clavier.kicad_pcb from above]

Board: 2 copper layers, 75.0 x 95.0 mm, 68 parts (0 on the bottom side), 18 nets.

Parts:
P1, P2: CONN_01X08; Pin_Header_Straight_2x04
P_PWSW1: CONN_01X02; Pin_Header_Straight_1x02
SW11, SW12, SW13, SW14, SW15, SW16, SW17, SW18, SW21, SW22, SW23, SW24, SW25, SW26, SW27, SW28, SW32, SW33, SW34, SW35, SW41, SW43, SW44, SW45, SW46, SW48, SW51, SW52, SW53, SW54, SW55, SW56, SW57, SW58, SW61, SW62, SW63, SW64, SW65, SW66, SW67, SW68, SW71, SW72, SW73, SW74, SW75, SW76, SW77, SW78, SW81, SW82, SW83, SW84, SW85, SW86, SW87, SW88: SW_PUSH_SMALL; bouton_large
SW31, SW36, SW37, SW38, SW42, SW47: SW_PUSH_SMALL; BOUTON_CLAVIER2.1
SW_PW1: SW_PUSH_SMALL; bouton_large

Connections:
unnamed: P1.1, SW18.2, SW28.2, SW38.2, SW48.2, SW58.2, SW68.2, SW78.2, SW88.2
unnamed: P1.2, SW17.2, SW27.2, SW37.2, SW47.2, SW57.2, SW67.2, SW77.2, SW87.2
unnamed: P1.3, SW16.2, SW26.2, SW36.2, SW46.2, SW56.2, SW66.2, SW76.2, SW86.2
unnamed: P1.4, SW15.2, SW25.2, SW35.2, SW45.2, SW55.2, SW65.2, SW75.2, SW85.2
unnamed: P1.5, SW14.2, SW24.2, SW34.2, SW44.2, SW54.2, SW64.2, SW74.2, SW84.2
unnamed: P1.6, SW13.2, SW23.2, SW33.2, SW43.2, SW53.2, SW63.2, SW73.2, SW83.2
unnamed: P1.7, SW12.2, SW22.2, SW32.2, SW42.2, SW52.2, SW62.2, SW72.2, SW82.2
unnamed: P1.8, SW11.2, SW21.2, SW31.2, SW41.2, SW51.2, SW61.2, SW71.2, SW81.2
unnamed: P2.1, SW11.1, SW12.1, SW13.1, SW14.1, SW15.1, SW16.1, SW17.1, SW18.1
unnamed: P2.2, SW21.1, SW22.1, SW23.1, SW24.1, SW25.1, SW26.1, SW27.1, SW28.1
unnamed: P2.3, SW31.1, SW32.1, SW33.1, SW34.1, SW35.1, SW36.1, SW37.1, SW38.1
unnamed: P2.4, SW41.1, SW42.1, SW43.1, SW44.1, SW45.1, SW46.1, SW47.1, SW48.1
unnamed: P2.5, SW51.1, SW52.1, SW53.1, SW54.1, SW55.1, SW56.1, SW57.1, SW58.1
unnamed: P2.6, SW61.1, SW62.1, SW63.1, SW64.1, SW65.1, SW66.1, SW67.1, SW68.1
unnamed: P2.7, SW71.1, SW72.1, SW73.1, SW74.1, SW75.1, SW76.1, SW77.1, SW78.1
unnamed: P2.8, SW81.1, SW82.1, SW83.1, SW84.1, SW85.1, SW86.1, SW87.1, SW88.1
unnamed: P_PWSW1.1, SW_PW1.2
unnamed: P_PWSW1.2, SW_PW1.1

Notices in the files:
Librecalc/Second_prototype/Electronics/proto2.0/calc.kicad_pcb:
Copyright Pierre Parent & Ael Gain
This is open hardware, you can use it under Cern Open Hardware License 1.2
parts and their libraries:
Copyright © 2012, Michel Stempin, All rights reserved
Licenced under Creative Commons CC BY-SA 3.0 license.
